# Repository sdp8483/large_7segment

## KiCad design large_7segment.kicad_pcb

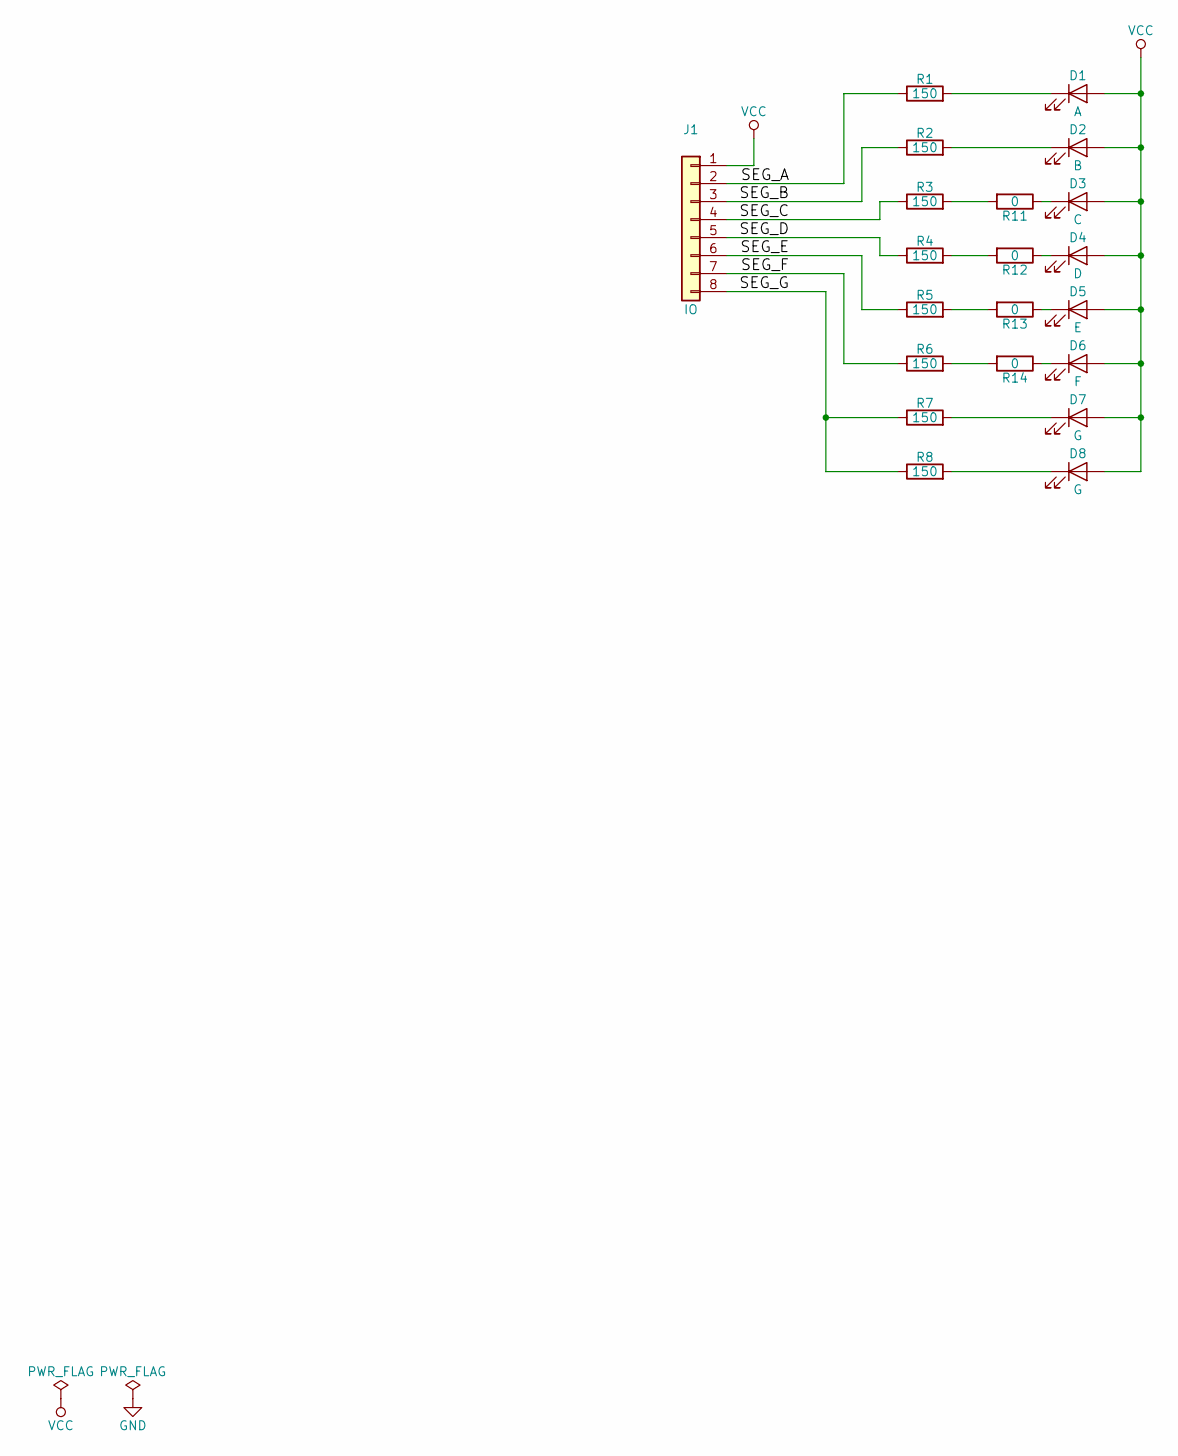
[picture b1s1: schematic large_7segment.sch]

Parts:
D1: A; LED_D5.0mm; Mfg Part Number NONE
D2: B; LED_D5.0mm; Mfg Part Number NONE
D3: C; LED_D5.0mm; Mfg Part Number NONE
D4: D; LED_D5.0mm; Mfg Part Number NONE
D5: E; LED_D5.0mm; Mfg Part Number NONE
D6: F; LED_D5.0mm; Mfg Part Number NONE
D7, D8: G; LED_D5.0mm; Mfg Part Number NONE
J1: IO; Header_01x08_SMDedTHT; Mfg Part Number NONE
R1, R2, R3, R4, R5, R6, R7, R8: 150; R_0805_HandSoldering; Mfg Part Number NONE
R11, R12, R13, R14: 0; R_1206_HandSoldering; Mfg Part Number NONE

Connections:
/SEG_A: J1.2, R1.1
/SEG_B: J1.3, R2.1
/SEG_C: J1.4, R3.1
/SEG_D: J1.5, R4.1
/SEG_E: J1.6, R5.1
/SEG_F: J1.7, R6.1
/SEG_G: J1.8, R7.1, R8.1
unnamed: D1.1 (K), R1.2
unnamed: D2.1 (K), R2.2
unnamed: D3.1 (K), R11.1
unnamed: D4.1 (K), R12.1
unnamed: D5.1 (K), R13.1
unnamed: D6.1 (K), R14.1
unnamed: D7.1 (K), R7.2
unnamed: D8.1 (K), R8.2
unnamed: R3.2, R11.2
unnamed: R4.2, R12.2
unnamed: R5.2, R13.2
unnamed: R6.2, R14.2
VCC: D1.2 (A), D2.2 (A), D3.2 (A), D4.2 (A), D5.2 (A), D6.2 (A), D7.2 (A), D8.2 (A), J1.1

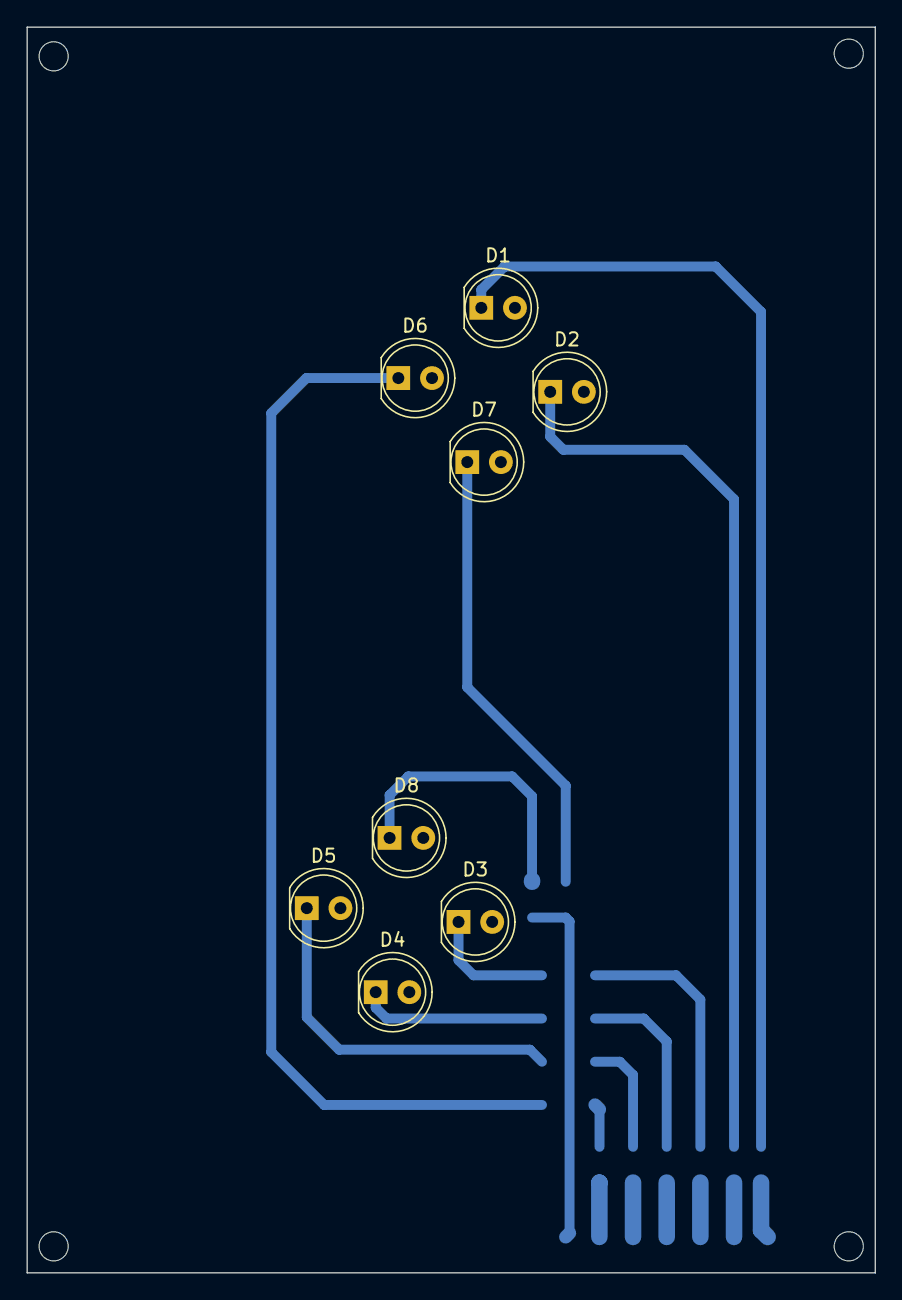
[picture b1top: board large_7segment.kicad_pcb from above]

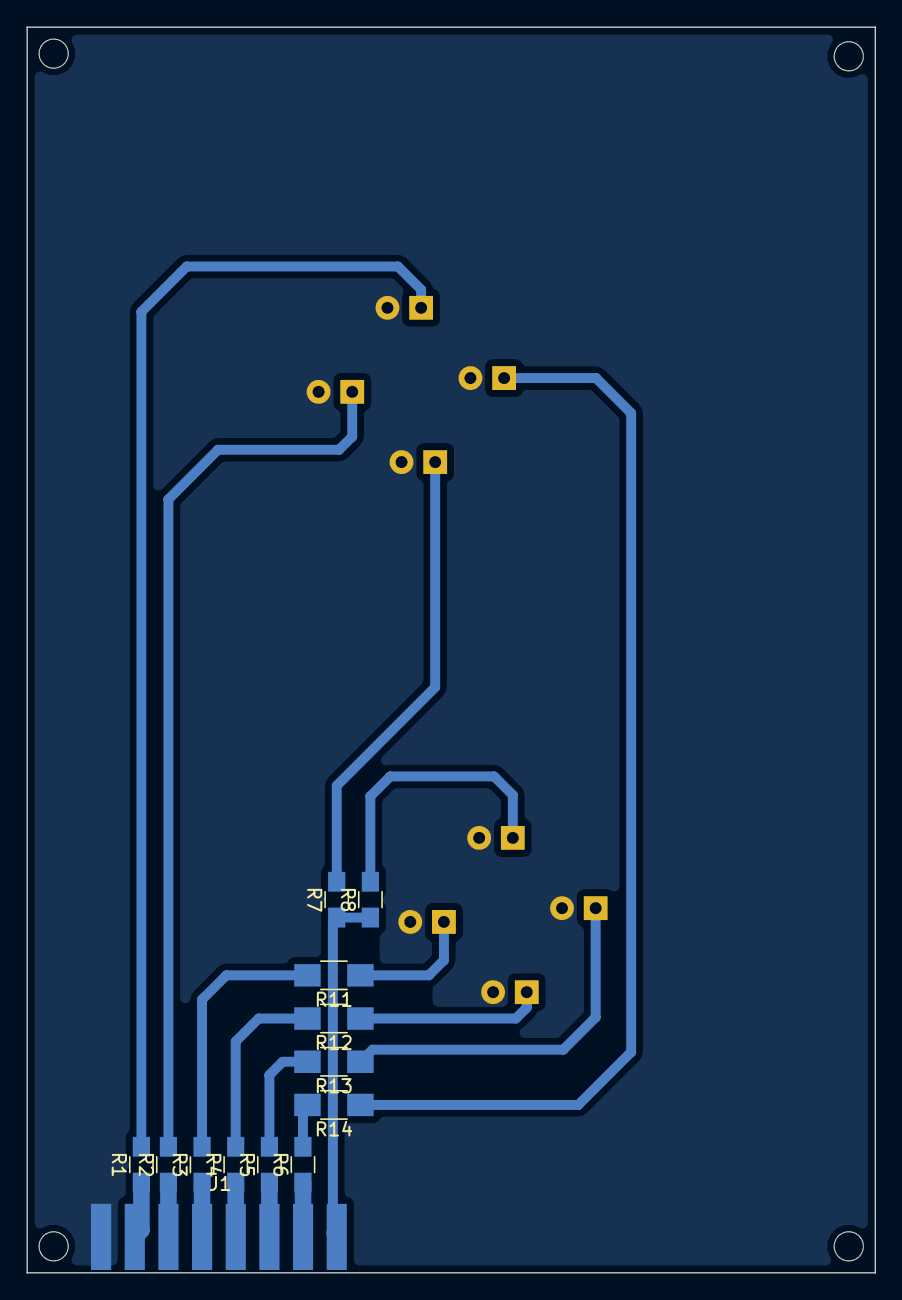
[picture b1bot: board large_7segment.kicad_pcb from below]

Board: 2 copper layers, 64.0 x 94.0 mm, 21 parts (13 on the bottom side), 20 nets.

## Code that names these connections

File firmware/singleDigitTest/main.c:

#include <msp430.h>
#include <stdint.h>

// Segment pin defines
#define SEG_A   BIT0
#define SEG_B   BIT1
#define SEG_C   BIT2
#define SEG_D   BIT3
#define SEG_E   BIT4
#define SEG_F   BIT5
#define SEG_G   BIT6
#define SEG_DP  BIT7
#define ALLSEG  SEG_A + SEG_B + SEG_C + SEG_D + SEG_E + SEG_F + SEG_G + SEG_DP

// Numeral segment defines
#define ZERO    SEG_A + SEG_B + SEG_C + SEG_D + SEG_E + SEG_F
#define ONE     SEG_B + SEG_C
#define TWO     SEG_A + SEG_B + SEG_G + SEG_E + SEG_D
#define THREE   SEG_A + SEG_B + SEG_C + SEG_D + SEG_G
#define FOUR    SEG_B + SEG_C + SEG_G + SEG_F
#define FIVE    SEG_A + SEG_F + SEG_G + SEG_C + SEG_D
#define SIX     SEG_A + SEG_F + SEG_G + SEG_C + SEG_D + SEG_E
#define SEVEN   SEG_A + SEG_B + SEG_C
#define EIGHT   SEG_A + SEG_B + SEG_C + SEG_D + SEG_E + SEG_F + SEG_G
#define NINE    SEG_A + SEG_B + SEG_C + SEG_D + SEG_F + SEG_G
#define HEX_A   SEG_A + SEG_B + SEG_C + SEG_E + SEG_F + SEG_G
#define HEX_B   SEG_C + SEG_D + SEG_E + SEG_F + SEG_G
#define HEX_C   SEG_A + SEG_D + SEG_E + SEG_F
#define HEX_D   SEG_B + SEG_C + SEG_D + SEG_E + SEG_G
#define HEX_E   SEG_A + SEG_D + SEG_E + SEG_F + SEG_G
#define HEX_F   SEG_A + SEG_E + SEG_F + SEG_G

void WDT_waitAsec(void);                        // use watchdog timer as 1 second interval, sleep during this time
uint8_t dispSegments(uint8_t value);

int main(void)
{
	WDTCTL = WDTPW | WDTHOLD;	                // stop watchdog timer

	SFRRPCR |= SYSRSTRE | SYSRSTUP;             // Enable internal pullup resistor on reset pin

	P1OUT |= ALLSEG;                            // preload segment pins high (high = off)
	P1DIR |= ALLSEG;                            // segment pins are output pins

	P2OUT |= BIT0 + BIT1 + BIT6 + BIT7;         // preload segment pins high
	P2DIR |= BIT0 + BIT1 + BIT6 + BIT7;         // set as output, makes ULP adviser happy
	PAOUT |= 0xFF;
	PADIR |= 0xFF;

	PM5CTL0 &= ~LOCKLPM5;                       // Disable the GPIO power-on default high-impedance mode to activate
                                                // previously configured port settings

	__enable_interrupt();                       // Enable global interrupts

	for(;;)                                     // loop forever!
	{
	    for(uint8_t i=0; i<16; i++){
            P1OUT |= ALLSEG;                        // disable all segments first
            P1OUT &= ~dispSegments(i);              // pull segments low
            WDT_waitAsec();
	    }
	}
}

void WDT_waitAsec()
{
    // WDT as 1s interval counter
    SFRIFG1 &= ~WDTIFG;
    WDTCTL = WDTPW + WDTSSEL_1 + WDTTMSEL + WDTCNTCL + WDTIS_4;
    SFRIE1 |= WDTIE;
    __bis_SR_register(LPM3_bits);               // Enter LPM3
}

// WDT interrupt service routine
#if defined(__TI_COMPILER_VERSION__) || defined(__IAR_SYSTEMS_ICC__)
#pragma vector = WDT_VECTOR
__interrupt void WDT_ISR(void)
#else
#error Compiler not supported!
#endif
{
        WDTCTL = WDTPW + WDTHOLD;               // Stop WDT
        __bic_SR_register_on_exit(LPM3_bits);   // Exit LPM3
}

uint8_t dispSegments(uint8_t value) {
    switch (value) {
    case(0):
        return ZERO;
    case(1):
        return ONE;
    case(2):
        return TWO;
    case(3):
        return THREE;
    case(4):
        return FOUR;
    case(5):
        return FIVE;
    case(6):
        return SIX;
    case(7):
        return SEVEN;
    case(8):
        return EIGHT;
    case(9):
        return NINE;
    case(10):
        return HEX_A;
    case(11):
        return HEX_B;
    case(12):
        return HEX_C;
    case(13):
        return HEX_D;
    case(14):
        return HEX_E;
    case(15):
        return HEX_F;
    default:
        return ZERO;

    } // end switch
} // end dispSegments()

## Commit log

2018-06-12 for loop display
